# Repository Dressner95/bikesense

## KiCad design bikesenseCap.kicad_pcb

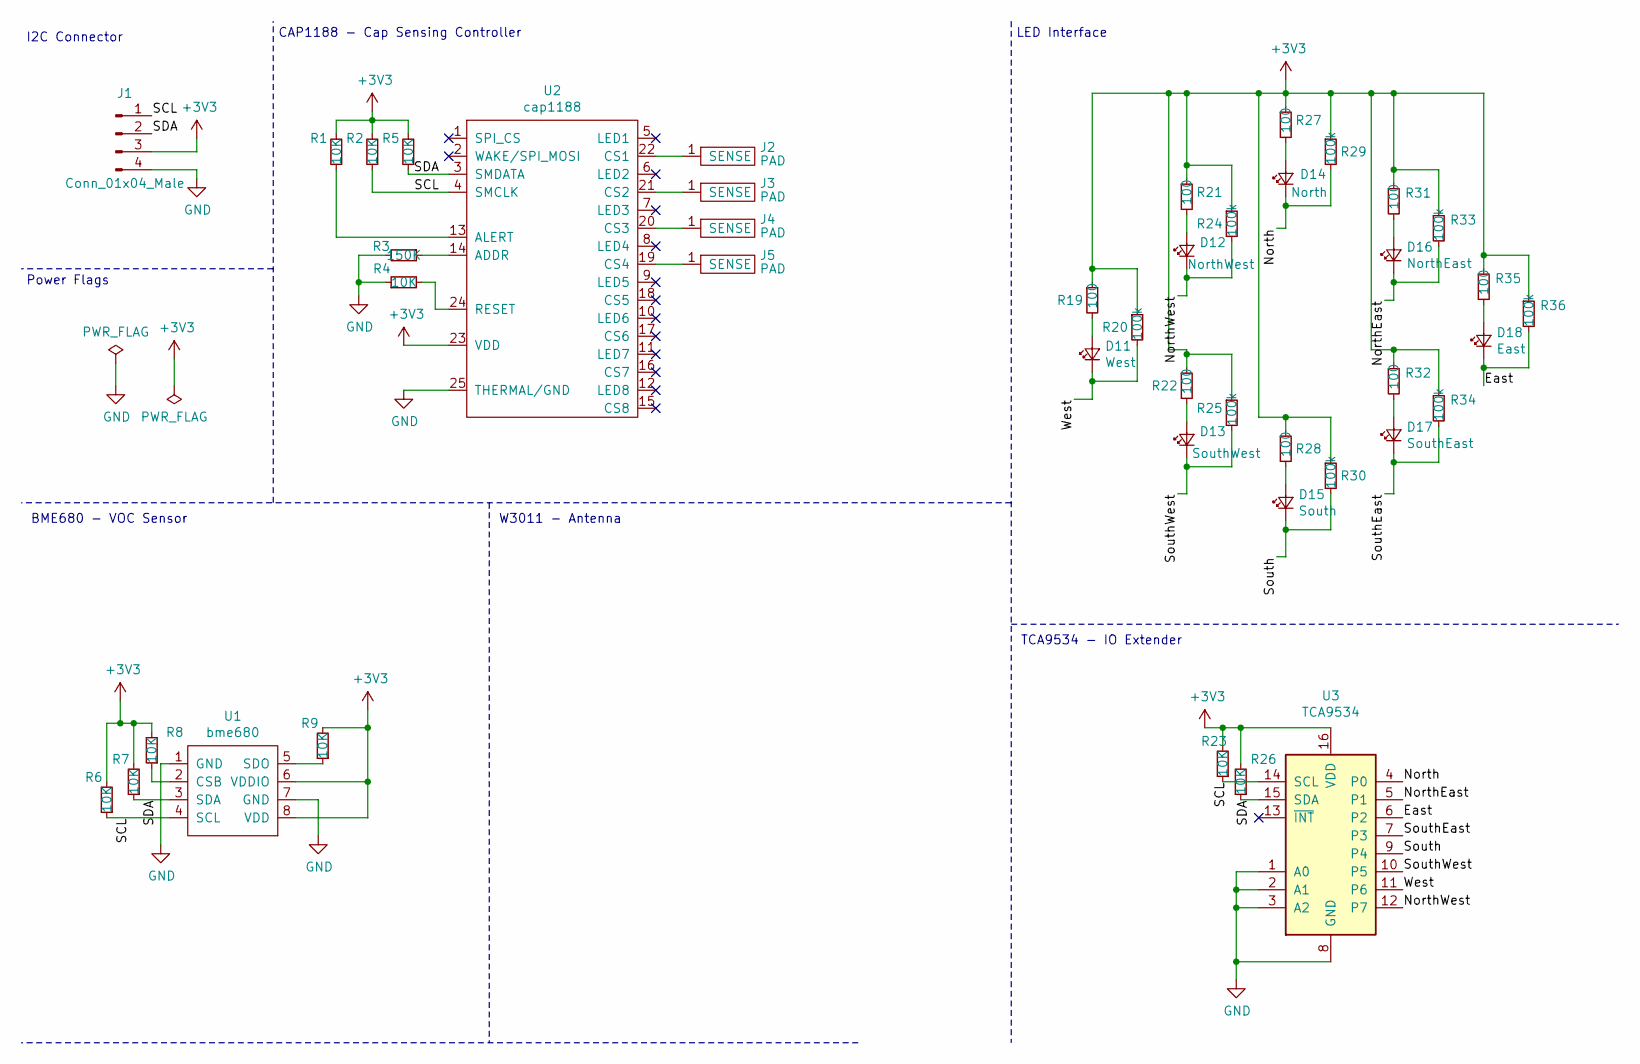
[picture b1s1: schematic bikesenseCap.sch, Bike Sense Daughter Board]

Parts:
D11: West; LED_1206_3216Metric_ReverseMount_Hole1.8x2.4mm
D12: NorthWest; LED_1206_3216Metric_ReverseMount_Hole1.8x2.4mm
D13: SouthWest; LED_1206_3216Metric_ReverseMount_Hole1.8x2.4mm
D14: North; LED_1206_3216Metric_ReverseMount_Hole1.8x2.4mm
D15: South; LED_1206_3216Metric_ReverseMount_Hole1.8x2.4mm
D16: NorthEast; LED_1206_3216Metric_ReverseMount_Hole1.8x2.4mm
D17: SouthEast; LED_1206_3216Metric_ReverseMount_Hole1.8x2.4mm
D18: East; LED_1206_3216Metric_ReverseMount_Hole1.8x2.4mm
J1: Conn_01x04_Male; HW4-2.0
J2, J3, J4, J5: PAD; SensePad
R1, R2, R4, R5, R6, R7, R8, R9, R23, R26: 10K; R_0603_HandSoldering
R3: 150K; R_0603_HandSoldering
R19, R21, R22, R27, R28, R31, R32, R35: 100; R_0603_HandSoldering
R20, R24, R25, R29, R30, R33, R34, R36: 100k; R_0603_HandSoldering
U1: bme680; BME680
U2: cap1188; QFN-24_4x4mm_Pitch0.5mm_NoMask
U3: TCA9534; SOIC-16_W7.5mm

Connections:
+3V3: J1.3, R1.2, R2.2, R5.2, R6.2, R7.2, R8.2, R9.2, R19.1, R20.1, R21.1, R22.1, R23.2, R24.1, R25.1, R26.2, R27.1, R28.1, R29.1, R30.1, R31.1, R32.1, R33.1, R34.1, R35.1, R36.1, U1.6 (VDDIO), U1.8 (VDD), U2.23 (VDD), U3.16 (VDD)
/East: D18.1 (K), R36.2, U3.6 (P2)
/North: D14.1 (K), R29.2, U3.4 (P0)
/NorthEast: D16.1 (K), R33.2, U3.5 (P1)
/NorthWest: D12.1 (K), R24.2, U3.12 (P7)
/SCL: J1.1, R2.1, R6.1, R23.1, U1.4 (SCL), U2.4 (SMCLK), U3.14 (SCL)
/SDA: J1.2, R5.1, R7.1, R26.1, U1.3 (SDA), U2.3 (SMDATA), U3.15 (SDA)
/South: D15.1 (K), R30.2, U3.9 (P4)
/SouthEast: D17.1 (K), R34.2, U3.7 (P3)
/SouthWest: D13.1 (K), R25.2, U3.10 (P5)
/West: D11.1 (K), R20.2, U3.11 (P6)
GND: J1.4, R3.2, R4.1, U1.1 (GND), U1.7 (GND), U2.25 (THERMAL/GND), U3.1 (A0), U3.2 (A1), U3.3 (A2), U3.8 (GND)
unnamed: D11.2 (A), R19.2
unnamed: D12.2 (A), R21.2
unnamed: D13.2 (A), R22.2
unnamed: D14.2 (A), R27.2
unnamed: D15.2 (A), R28.2
unnamed: D16.2 (A), R31.2
unnamed: D17.2 (A), R32.2
unnamed: D18.2 (A), R35.2
unnamed: J2.1, U2.22 (CS1)
unnamed: J3.1, U2.21 (CS2)
unnamed: J4.1, U2.20 (CS3)
unnamed: J5.1, U2.19 (CS4)
unnamed: R1.1, U2.13 (ALERT)
unnamed: R3.1, U2.14 (ADDR)
unnamed: R4.2, U2.24 (RESET)
unnamed: R8.1, U1.2 (CSB)
unnamed: R9.1, U1.5 (SDO)

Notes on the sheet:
I2C Connector
Power Flags
BME680 - VOC Sensor
CAP1188 - Cap Sensing Controller
LED Interface
TCA9534 - IO Extender
W3011 - Antenna

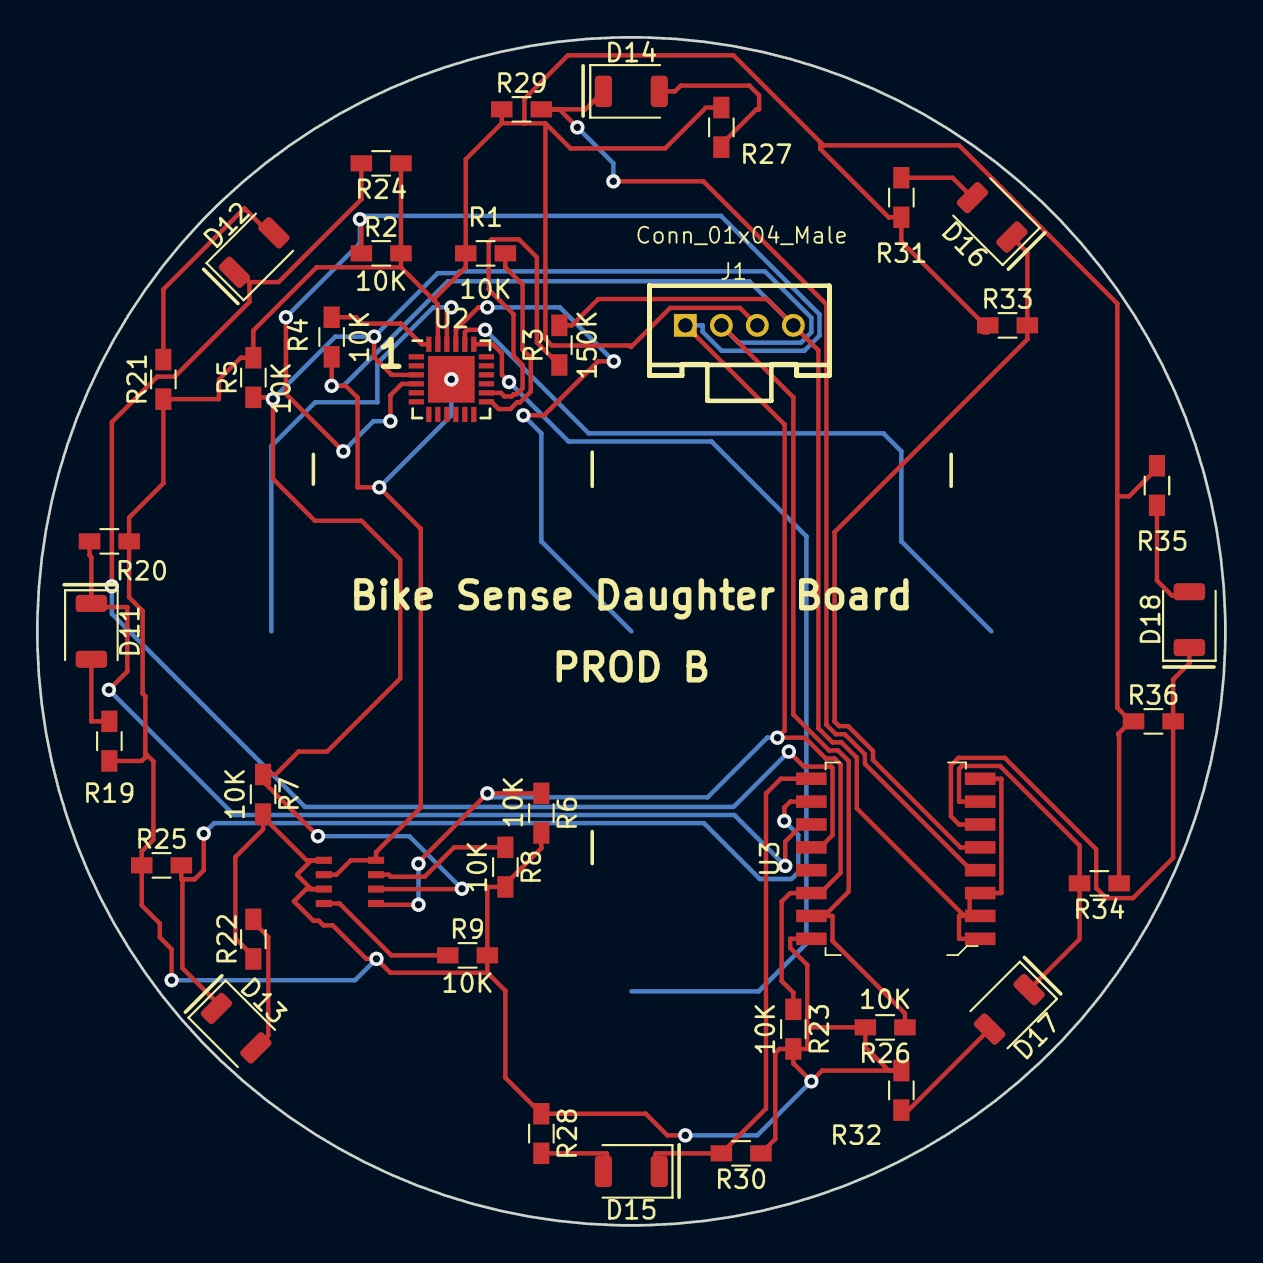
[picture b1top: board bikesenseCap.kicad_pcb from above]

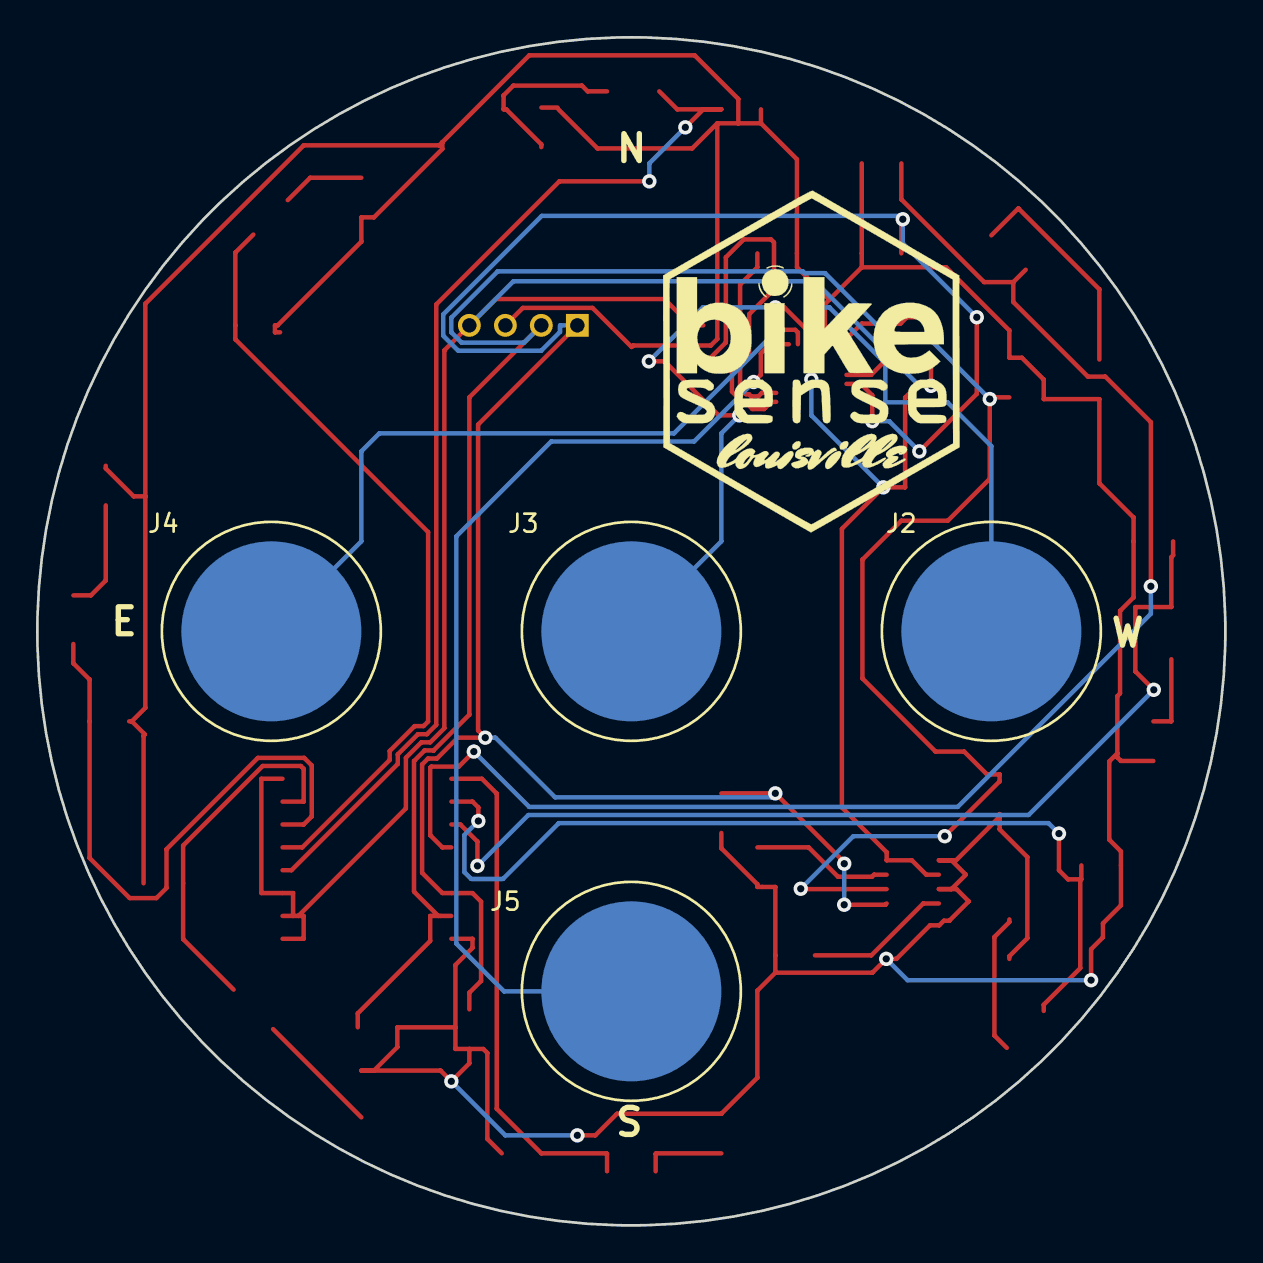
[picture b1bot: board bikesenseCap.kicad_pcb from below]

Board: 2 copper layers, 66.0 x 66.0 mm, 43 parts (4 on the bottom side), 29 nets.

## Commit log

2018-11-07 INital commit
2018-11-15 Routing updated
2019-01-03 up to revB
2019-01-29 Added particle libs
2019-02-17 REV C
2019-03-04 Added MISSING trace
2019-07-31 Removed GPS and CAPsenseing led from broad
